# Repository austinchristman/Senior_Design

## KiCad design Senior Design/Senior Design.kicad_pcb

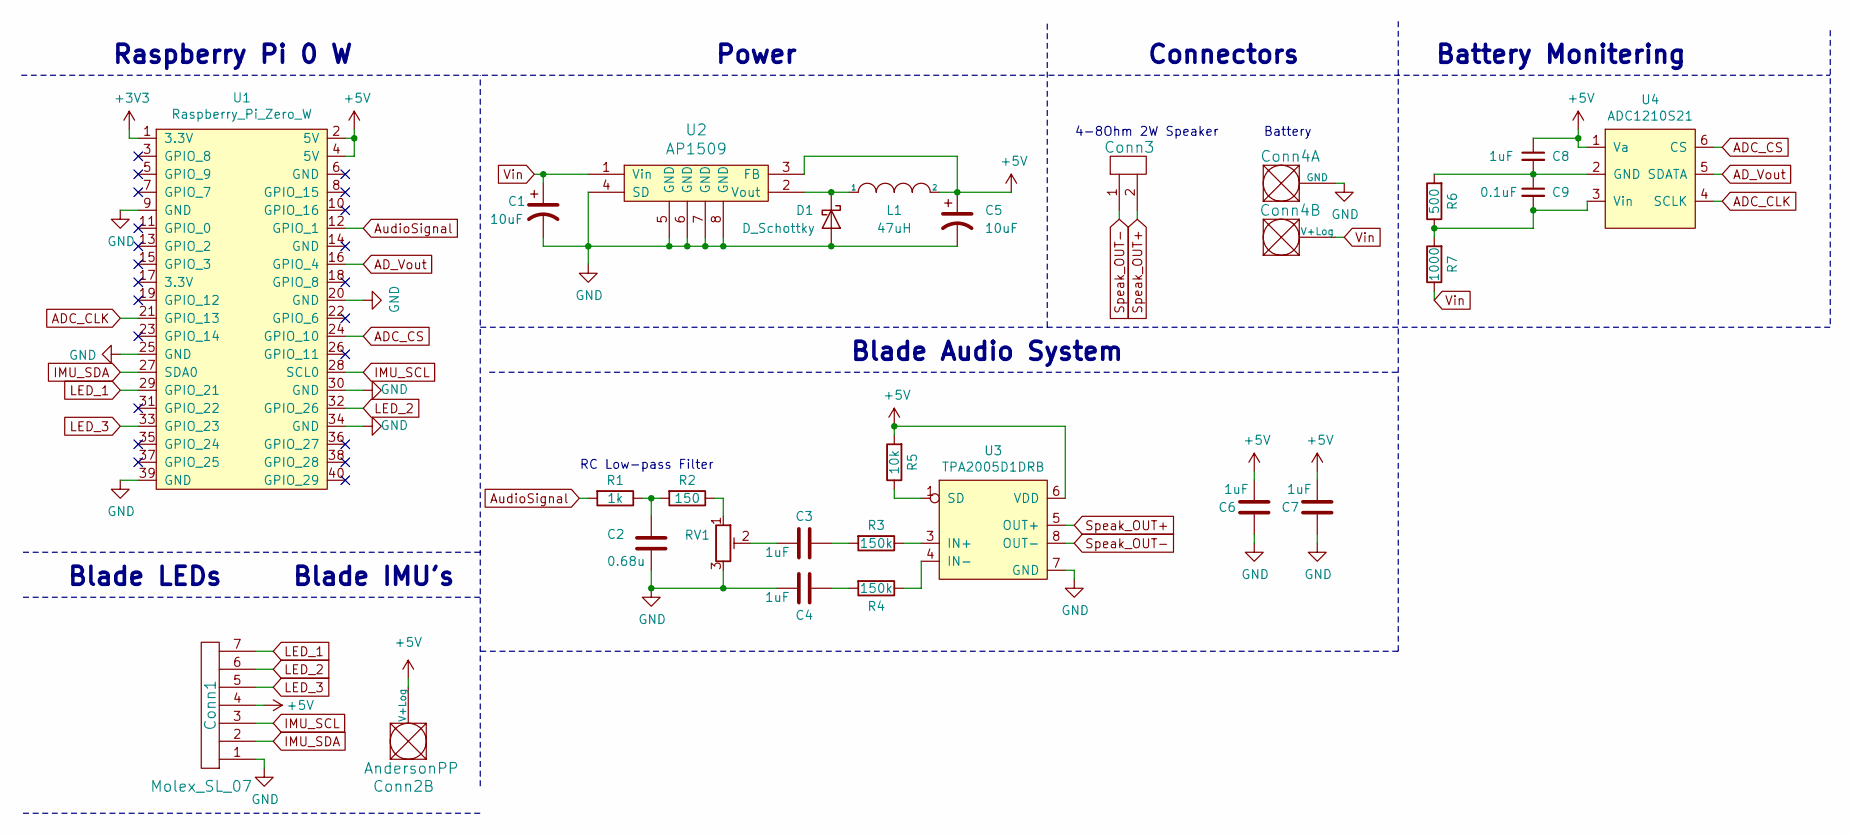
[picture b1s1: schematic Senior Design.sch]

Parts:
C1, C5: 10uF; C_0603_1608Metric_Pad1.05x0.95mm_HandSolder
C2: 0.68u; C_0603_1608Metric_Pad1.05x0.95mm_HandSolder
C3, C4, C6, C7, C8: 1uF; C_0603_1608Metric_Pad1.05x0.95mm_HandSolder
C9: 0.1uF; C_0603_1608Metric_Pad1.05x0.95mm_HandSolder
Conn1: Molex_SL_07; MOLEX_SL_07_Horizontal
Conn2: AndersonPP; Anderson_1_Horizontal
Conn3: Molex_SL_02; MOLEX_SL_02_Horizontal
Conn4: AndersonPP; Anderson_2_Horizontal_Side_by_Side
D1: D_Schottky; D_0603_1608Metric_Pad1.05x0.95mm_HandSolder
L1: 47uH; L_0603_1608Metric_Pad1.05x0.95mm_HandSolder
R1: 1k; R_0603_1608Metric_Pad1.05x0.95mm_HandSolder
R2: 150; R_0603_1608Metric_Pad1.05x0.95mm_HandSolder
R3, R4: 150k; R_0603_1608Metric_Pad1.05x0.95mm_HandSolder
R5: 10k; R_0603_1608Metric_Pad1.05x0.95mm_HandSolder
R6: 500; R_0603_1608Metric_Pad1.05x0.95mm_HandSolder
R7: 1000; R_0603_1608Metric_Pad1.05x0.95mm_HandSolder
RV1: R_POT_TRIM; Potentiometer_Bourns_3214J_Horizontal
U1: Raspberry_Pi_Zero_W
U2: AP1509; SO-8_5.3x6.2mm_P1.27mm
U3: TPA2005D1DRB; TSSOP-8_3x3mm_P0.65mm
U4: ADC1210S21; SOT-23-6_Handsoldering

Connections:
+3V3: U1.1 (3.3V)
+5V: C5.1, C6.2, C7.2, C8.1, Conn1.4, Conn2.2 (V+Log), L1.2, R5.2, U1.2 (5V), U1.4 (5V), U2.3 (FB), U3.6 (VDD), U4.1 (Va)
ADC_CLK: U1.21 (GPIO_13), U4.4 (SCLK)
ADC_CS: U1.24 (GPIO_10), U4.6 (CS)
AD_Vout: U1.16 (GPIO_4), U4.5 (SDATA)
AudioSignal: R1.2, U1.12 (GPIO_1)
GND: C1.2, C2.2, C4.2, C5.2, C6.1, C7.1, Conn1.1, Conn4.1 (GND), D1.2 (A), RV1.3, U1.9 (GND), U1.20 (GND), U1.25 (GND), U1.30 (GND), U1.34 (GND), U1.39 (GND), U2.4 (SD), U2.5 (GND), U2.6 (GND), U2.7 (GND), U2.8 (GND), U3.7 (GND)
IMU_SCL: Conn1.3, U1.28 (SCL0)
IMU_SDA: Conn1.2, U1.27 (SDA0)
LED_1: Conn1.7, U1.29 (GPIO_21)
LED_2: Conn1.6, U1.32 (GPIO_26)
LED_3: Conn1.5, U1.33 (GPIO_23)
unnamed: C2.1, R1.1, R2.2
unnamed: C3.1, R3.2
unnamed: C3.2, RV1.2
unnamed: C4.1, R4.2
unnamed: C8.2, C9.1, R6.2, U4.2 (GND)
unnamed: C9.2, R6.1, R7.2, U4.3 (Vin)
unnamed: D1.1 (K), L1.1, U2.2 (Vout)
unnamed: R2.1, RV1.1
unnamed: R3.1, U3.3 (IN+)
unnamed: R4.1, U3.4 (IN-)
unnamed: R5.1, U3.1 (SD)
Speak_OUT+: Conn3.2, U3.5 (OUT+)
Speak_OUT-: Conn3.1, U3.8 (OUT-)
Vin: C1.1, Conn4.2 (V+Log), R7.1, U2.1 (Vin)

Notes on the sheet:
Raspberry Pi 0 W
Blade LEDs
Blade IMU's
Blade Audio System
RC Low-pass Filter
Power
Connectors
4-8Ohm 2W Speaker
Battery
Battery Monitering

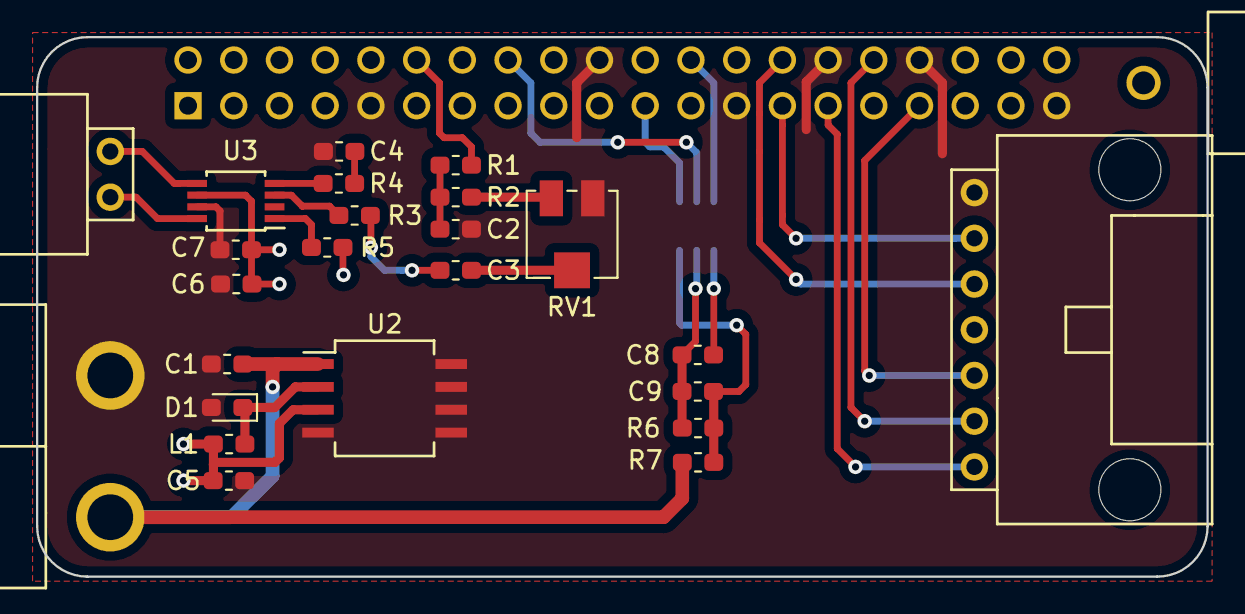
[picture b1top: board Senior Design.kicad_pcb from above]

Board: 2 copper layers, 65.0 x 30.0 mm, 27 parts (1 on the bottom side), 25 nets.

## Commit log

2020-09-27 uploaded project
2020-11-10 update
    ddds
